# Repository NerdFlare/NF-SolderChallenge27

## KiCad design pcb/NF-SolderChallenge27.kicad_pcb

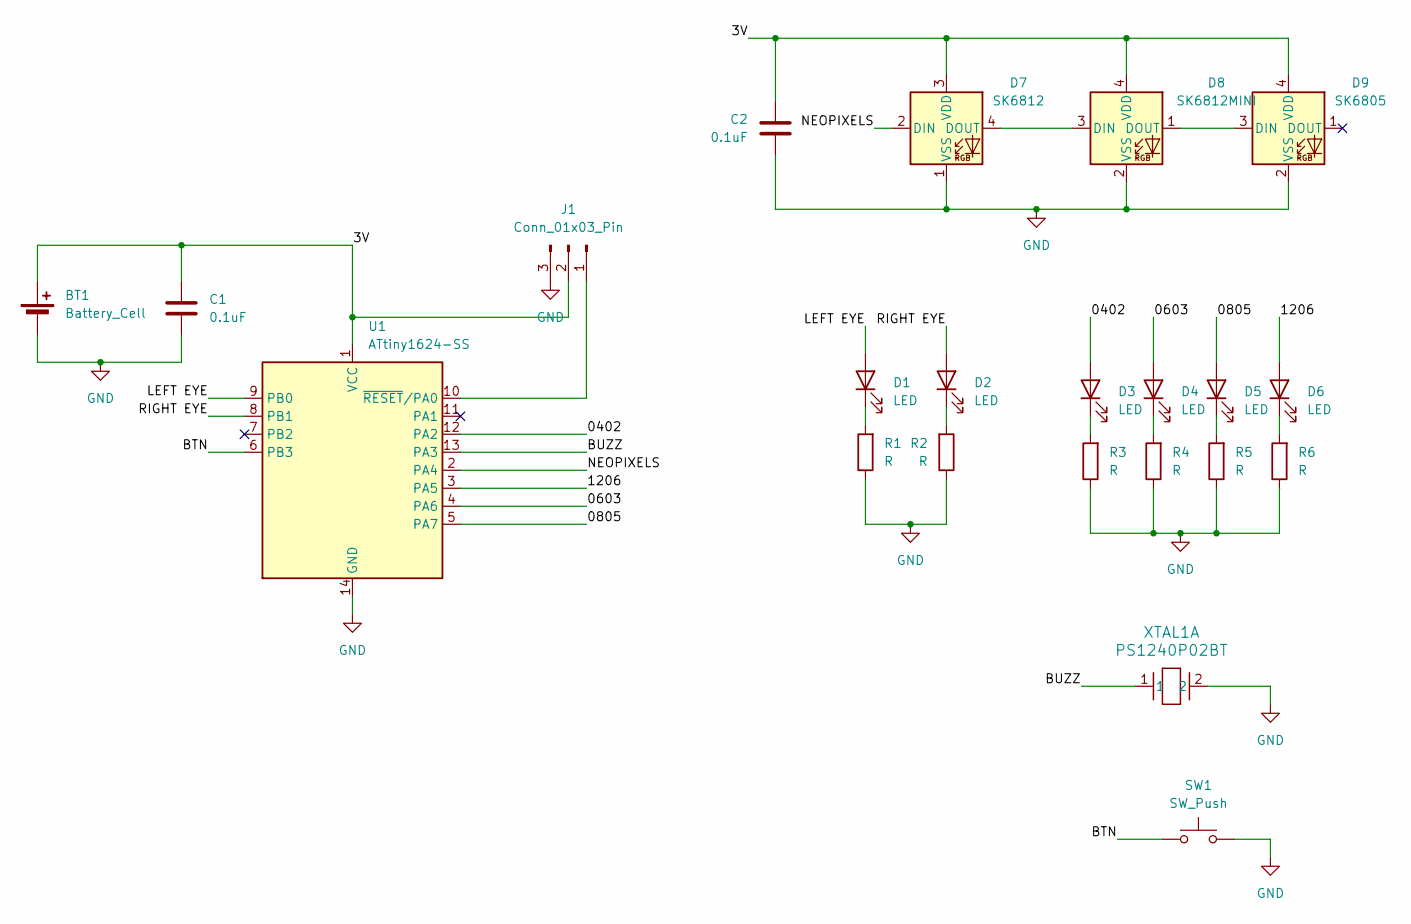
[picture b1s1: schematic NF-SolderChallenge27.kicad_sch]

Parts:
BT1: Battery_Cell; BAT-SMD_BS-24-B4AK014
C1, C2: 0.1uF; C_1206_3216Metric_Pad1.33x1.80mm_HandSolder
D1, D2: LED; LED_D5.0mm
D3: LED; LED_0402_1005Metric_Pad0.77x0.64mm_HandSolder
D4: LED; LED_0603_1608Metric_Pad1.05x0.95mm_HandSolder
D5: LED; LED_0805_2012Metric_Pad1.15x1.40mm_HandSolder
D6: LED; LED_1206_3216Metric_Pad1.42x1.75mm_HandSolder
D7: SK6812; LED_SK6812_PLCC4_5.0x5.0mm_P3.2mm
D8: SK6812MINI; LED_SK6812MINI_PLCC4_3.5x3.5mm_P1.75mm
D9: SK6805; LED_SK6805_PLCC4_2.4x2.7mm_P1.3mm
J1: Conn_01x03_Pin; UPDI_1x03_P2.54mm_SMT
R1, R2: R; R_Axial_DIN0207_L6.3mm_D2.5mm_P7.62mm_Horizontal
R3: R; R_0402_1005Metric_Pad0.72x0.64mm_HandSolder
R4: R; R_0603_1608Metric_Pad0.98x0.95mm_HandSolder
R5: R; R_0805_2012Metric_Pad1.20x1.40mm_HandSolder
R6: R; R_1206_3216Metric_Pad1.30x1.75mm_HandSolder
SW1: SW_Push; SW_SPST_PTS645Sx43SMTR92
U1: ATtiny1624-SS; SOIC-14_3.9x8.7mm_P1.27mm
XTAL1: PS1240P02BT; XTAL_PS1240P02BT_TDK

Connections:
/3V: BT1.1 (+), C1.1, C2.1, D7.3 (VDD), D8.4 (VDD), D9.4 (VDD), J1.2, U1.1 (VCC)
/0402: D3.2 (A), U1.12 (PA2)
/0603: D4.2 (A), U1.4 (PA6)
/0805: D5.2 (A), U1.5 (PA7)
/1206: D6.2 (A), U1.3 (PA5)
/BTN: SW1.1, U1.6 (PB3)
/BUZZ: U1.13 (PA3), XTAL1.1
/LEFT EYE: D1.2 (A), U1.9 (PB0)
/NEOPIXELS: D7.2 (DIN), U1.2 (PA4)
/RIGHT EYE: D2.2 (A), U1.8 (PB1)
GND: BT1.2 (-), C1.2, C2.2, D7.1 (VSS), D8.2 (VSS), D9.2 (VSS), J1.3, R1.1, R2.1, R3.1, R4.1, R5.1, R6.1, SW1.2, U1.14 (GND), XTAL1.2
unnamed: D1.1 (K), R1.2
unnamed: D2.1 (K), R2.2
unnamed: D3.1 (K), R3.2
unnamed: D4.1 (K), R4.2
unnamed: D5.1 (K), R5.2
unnamed: D6.1 (K), R6.2
unnamed: D7.4 (DOUT), D8.3 (DIN)
unnamed: D8.1 (DOUT), D9.3 (DIN)
unnamed: J1.1, U1.10 (~RESET/PA0)

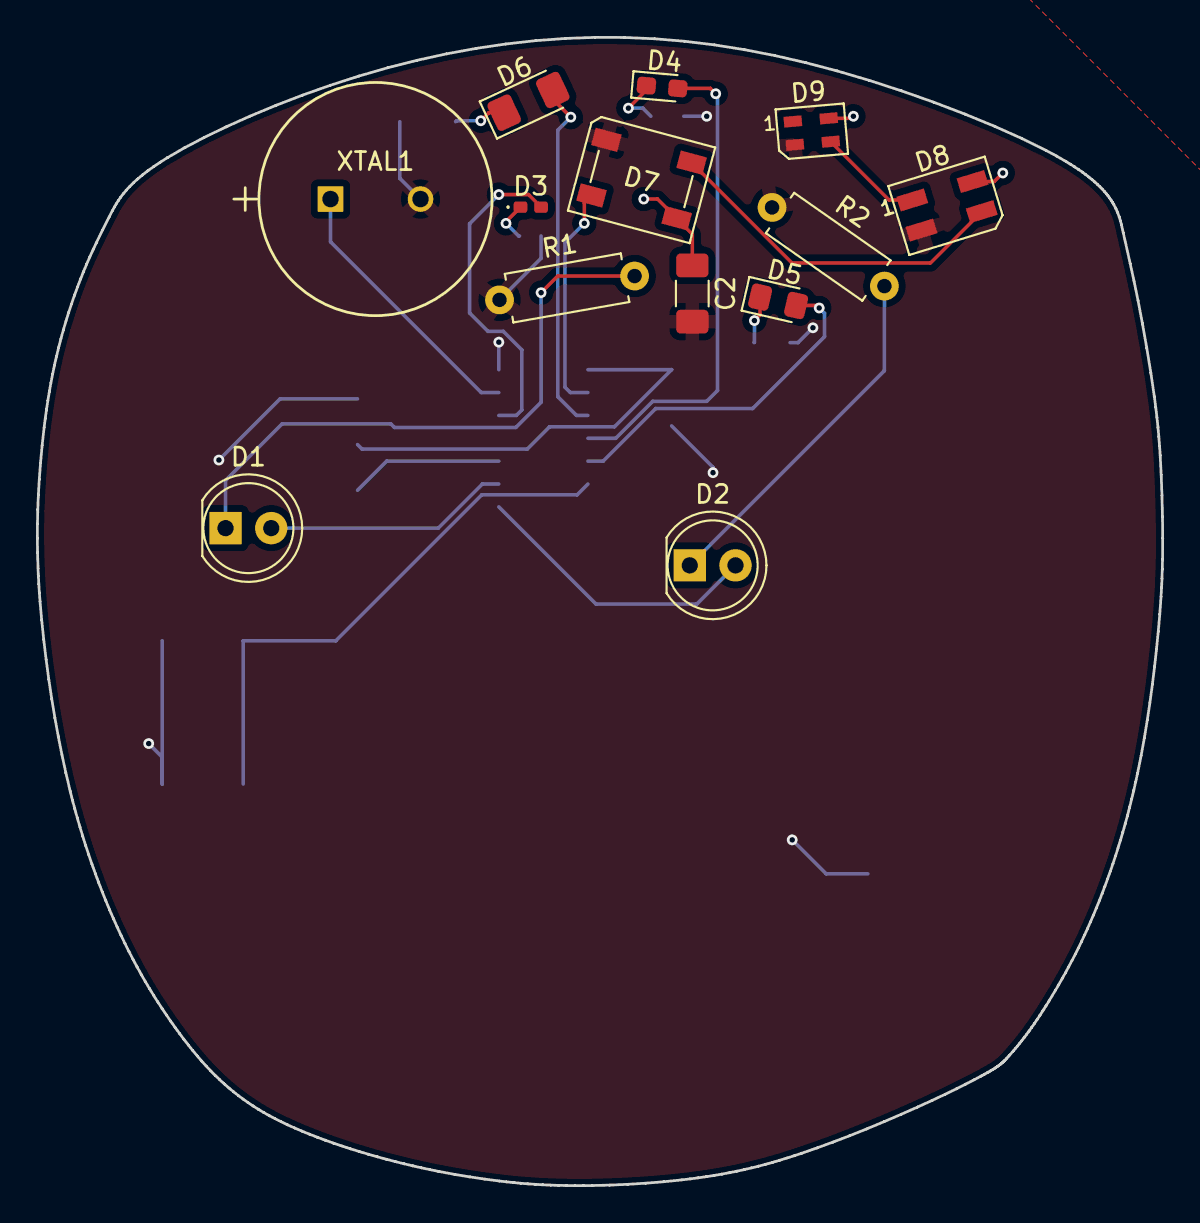
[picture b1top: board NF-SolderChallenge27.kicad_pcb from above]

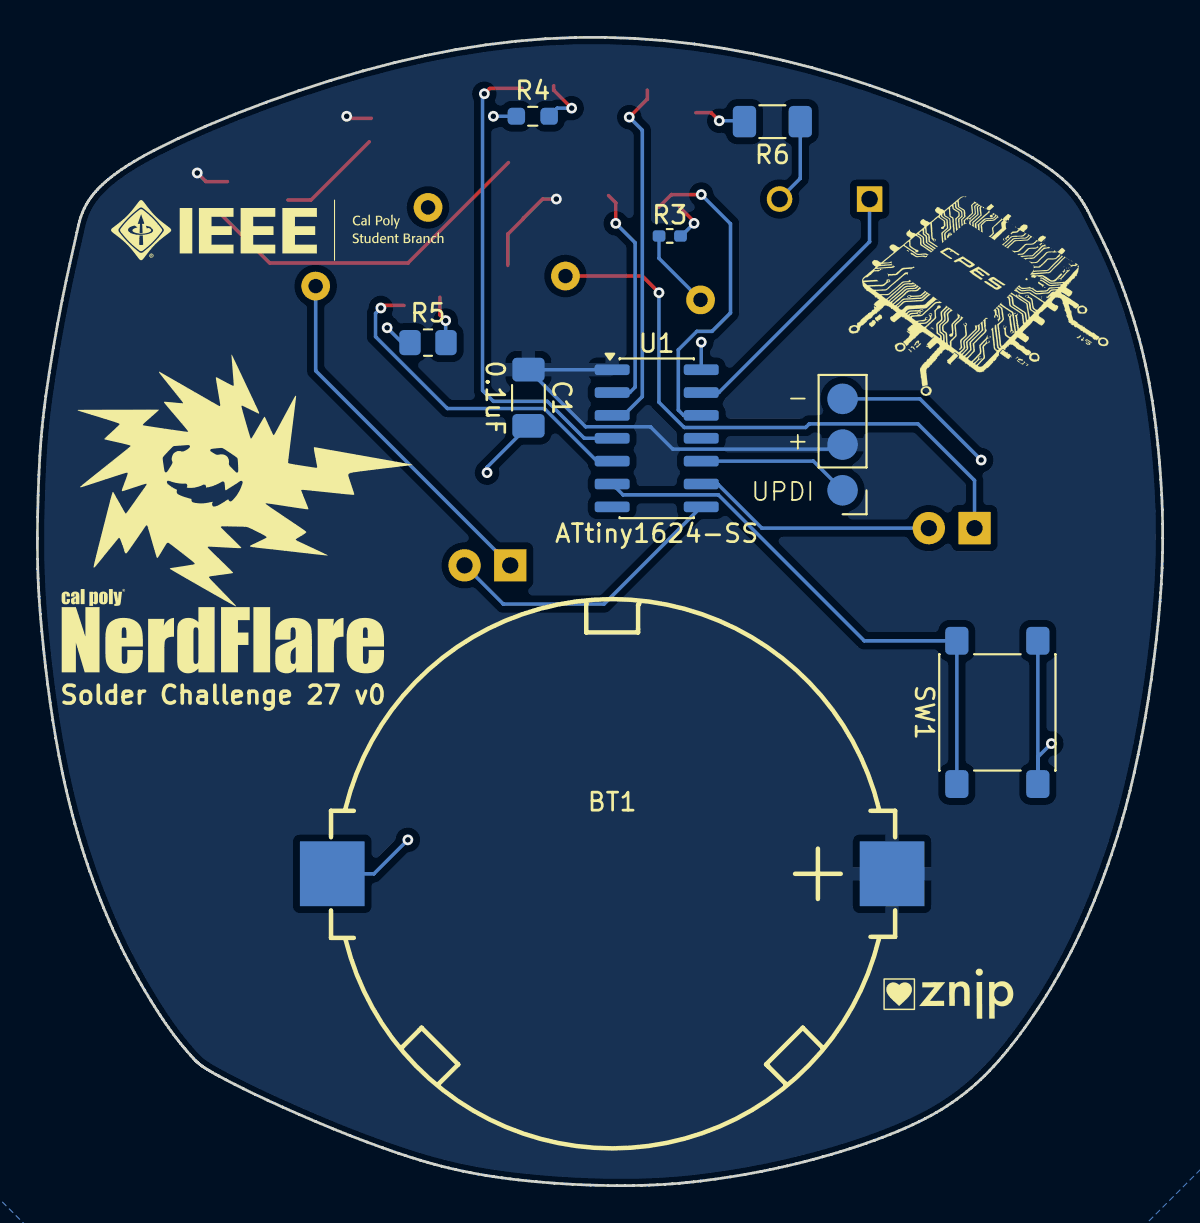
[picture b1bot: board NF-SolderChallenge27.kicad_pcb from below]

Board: 2 copper layers, 62.5 x 63.8 mm, 22 parts (9 on the bottom side), 20 nets.

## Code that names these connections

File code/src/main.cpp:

#include <Arduino.h>
#include <EEPROM.h>
#include <tinyNeoPixel.h>

const int D1 = PIN_PB0; // Left eye
const int D2 = PIN_PB1; // Right eye
const int D3 = PIN_PA2; // 0402
const int D4 = PIN_PA6; // 0603
const int D5 = PIN_PA7; // 0805
const int D6 = PIN_PA5; // 1206
const int LEDS[] = {D1,D2,D3,D4,D5,D6};

const int NEOPIXEL = PIN_PA4; // Neopixels
const int PIXEL_COUNT = 3;
tinyNeoPixel strip = tinyNeoPixel(PIXEL_COUNT, NEOPIXEL, NEO_GRB);

const int BUTTON = PIN_PB3; // Button
bool pressed = true;

const int BUZZ = PIN_PA3; // Buzzer

//rainbow animation
int rainbox_index = 0;
// LED animation 
bool flipflop = true;

// Input a value 0 to 255 to get a color value.
// The colours are a transition r - g - b - back to r.
uint32_t Wheel(byte WheelPos) {
  WheelPos = 255 - WheelPos;
  if (WheelPos < 85) {
    return strip.Color(255 - WheelPos * 3, 0, WheelPos * 3);
  }
  if (WheelPos < 170) {
    WheelPos -= 85;
    return strip.Color(0, WheelPos * 3, 255 - WheelPos * 3);
  }
  WheelPos -= 170;
  return strip.Color(WheelPos * 3, 255 - WheelPos * 3, 0);
}

void setup() {

  for(int i = 0; i < 6; i++){
    pinMode(LEDS[i], OUTPUT);
    digitalWrite(LEDS[i], LOW);
  }
  pinMode(NEOPIXEL, OUTPUT);
  strip.setBrightness(50);
  pinMode(BUTTON, INPUT_PULLUP);
  pinMode(BUZZ, OUTPUT);

}

void loop() {

  //Handle Button
  if (digitalRead(BUTTON) == LOW && !pressed){
    pressed = true;
    tone(BUZZ, 1000);
    delay(1000);     // Short delay to debounce button.
  }
  if (digitalRead(BUTTON) == HIGH){
    pressed = false;
    noTone(BUZZ);
    delay(20);
  }

  //Flash LEDs
  for(int i = 0; i < 6; i++){
    digitalWrite(LEDS[i], flipflop);
    delay(100);
  }
  flipflop = !flipflop;

  //Rainbow cycle the neopixels
  for (int i = strip.numPixels() - 1; i >= 0; i--) {
    strip.setPixelColor(i, Wheel(((i * 64) + rainbox_index) & 255));
    rainbox_index = (rainbox_index+1)%256;
  }
  strip.show();

}
